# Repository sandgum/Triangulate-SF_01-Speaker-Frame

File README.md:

# Triangulate-SF_01-Speaker-Frame

*AI Use: No AI was used to generate any journal entries at all. AI was only used for electronics review and firmware help*

## Description
The SF_01 is a 24-inch digital picture frame running Android on a Raspberry Pi CM4. The Pi pushes an image to an off-the-shelf IPS monitor from LG through HDMI, and has wireless and USB peripheral support for touch displays, keyboards, and other HIDs.

The SF_01 also has a total 220W RMS speaker system on board, with 6 3.5-inch bass-mid woofers, and 4 0.75-inch tweeterspointing outwards from all four corners.

The frame itself is 3D-printed, with a large stand secured by VESA mount screws driven into the back of the monitor.

The frame has a separate circuit on board for audio playback, with an ESP32-S3 WROOM 2 module at its heart. It decodes a stereo Bluetooth A2DP stream, performs DSP calculations on board, and outputs two different I2S signals (one for the bass-mid woofers, the other for the tweeters).

After going through a DAC, the audio signals are routed through a custom analog multiplexer circuit to all 10 drivers, dynamically switching stereo output between drivers depending on the orientation of the frame.

The ESP32 appears in a device's Bluetooth list as a speaker, and it also runs a GATT server that is controlled by a Bluetooth LE connection via a custom iPhone app. Equalisers and crossovers can be set in the app.

### Woofer Layout

```
(1) ---------- (2)
(3)            (4)
(5) ---------- (6)
```

### Tweeter Layout

```
(1) ---------- (2)
 |              |
(3) ---------- (4)
```

**Landscape Orientation:**
* Left Channel:
* Woofers 1, 3, 5
* Tweeters 1, 3

* Right Channel:
* Woofers 2, 4, 6
* Tweeters 2, 4
  
**Portrait Orientation:**

* Left Channel:
* Woofers 5, 6
* Tweeters 3, 4

* Right Channel:
* Woofers 1, 2
* Tweeters 1, 2

* **Centre Channel: (Average of Right and Left):**
* Woofers 3, 4

## Built Prototype Images

## 3D Model Images

## PCB Schematics

**Raspberry Pi Circuit**

**DAC and Analog Multiplexer Circuit**

**ESP32 WROVER E Circuit**

**Subwoofer Amplifiers**

**Tweeter Amplifiers**

**Environmental and Orientation Sensors**

**Power Circuitry**

## PCB Layout

**Top Layer**

**Inner Layer 1 (GND Plane)**

**Inner Layer 2**

**Bottom Layer**

**3D Model**

## Bill Of Materials

Quantities are **per board**. Prices are LCSC unit pricing at low volume and drop at quantity. Everything except the Compute Module, drivers and panel is sourced from LCSC.

### Board Components

| Designators | Qty | Value | Part Number | Manufacturer | Package | Description | Unit (USD) | Ext. (USD) | LCSC |
|---|---|---|---|---|---|---|---|---|---|
| C1, C4, C5, C7, C9, C14, C17, C19, C23, C26, C28, C31, C34, C37, C38, C39, C42, C43, C45, C47, C50, C53, C72, C74, C80, C81, C106, C109, C135, C138, C163, C166, C185, C186, C189 | 35 | 100nF | CL10B104KB8NNNC | Samsung Electro-Mechanics | 0603 | 100nF ±10% 50V X7R 0603 | 0.0142 | 0.50 | [C1591](https://www.lcsc.com/product-detail/C1591.html) |
| C49, C52, C61, C62, C67, C68, C79, C82, C92, C93, C94, C95, C107, C108, C119, C120, C121, C122, C136, C137, C149, C150, C151, C152, C164, C165, C177, C178, C179, C180 | 30 | 1nF | CL10C102JB8NNNC | Samsung Electro-Mechanics | 0603 | 1nF ±5% 50V C0G 0603 | 0.0076 | 0.23 | [C163508](https://www.lcsc.com/product-detail/C163508.html) |
| C2, C8, C12, C13, C40, C41, C44, C46, C48, C75, C76, C77, C102, C103, C105, C131, C132, C134, C157, C158, C159, C160, C162, C188, C190 | 25 | 1uF | CL10B105KA8NNNC | Samsung Electro-Mechanics | 0603 | 1uF ±10% 25V X7R 0603 | 0.0218 | 0.55 | [C29936](https://www.lcsc.com/product-detail/C29936.html) |
| C24, C63, C64, C69, C70, C96, C97, C98, C99, C123, C124, C125, C126, C153, C154, C155, C156, C181, C182, C183, C184 | 21 | 10nF | GRM1885C1H103JA01D | muRata | 0603 | 10nF ±5% 50V C0G 0603 | 0.0547 | 1.15 | [C85973](https://www.lcsc.com/product-detail/C85973.html) |
| C55, C56, C57, C58, C84, C85, C86, C87, C111, C112, C113, C114, C141, C142, C143, C144, C169, C170, C171, C172 | 20 | 220nF | CL10B224KB8NNNC | Samsung Electro-Mechanics | 0603 | 220nF ±10% 50V X7R 0603 | 0.0121 | 0.24 | [C64705](https://www.lcsc.com/product-detail/C64705.html) |
| C59, C60, C65, C66, C88, C89, C90, C91, C115, C116, C117, C118, C145, C146, C147, C148, C173, C174, C175, C176 | 20 | 680nF | CGA3E3X5R1H684KT0Y0N | TDK | 0603 | 680nF ±10% 50V X5R 0603 | 0.1052 | 2.10 | [C694504](https://www.lcsc.com/product-detail/C694504.html) |
| C10, C11, C35, C36, C71 | 5 | 2.2nF | CL10B222KB8NNNC | Samsung Electro-Mechanics | 0603 | 2.2nF ±10% 50V X7R 0603 | 0.0061 | 0.03 | [C16033](https://www.lcsc.com/product-detail/C16033.html) |
| C20, C21, C29, C30 | 4 | 2.2uF | CL10A225KA8NNNC | Samsung Electro-Mechanics | 0603 | 2.2uF ±10% 25V X5R 0603 | 0.0231 | 0.09 | [C57895](https://www.lcsc.com/product-detail/C57895.html) |
| C6 | 1 | 22uF | CL10A226MP8NUNE | Samsung Electro-Mechanics | 0603 | 22uF ±20% 10V X5R 0603 | 0.0825 | 0.08 | [C86295](https://www.lcsc.com/product-detail/C86295.html) |
| C187 | 1 | 6.8pF | CC0603BRNPO9BN6R8 | YAGEO | 0603 | 6.8pF 50V NP0 0603 | 0.0038 | 0.00 | [C519114](https://www.lcsc.com/product-detail/C519114.html) |
| C130 | 1 | 7.5nF | GRM1885C1H752JA01D | muRata | 0603 | 7.5nF ±5% 50V C0G 0603 | 0.0156 | 0.02 | [C907758](https://www.lcsc.com/product-detail/C907758.html) |
| C100, C101, C129 | 3 | 10uF/50V | GRM32ER71H106KA12L | muRata | 1210 | 10uF ±10% 50V X7R 1210 | 0.3758 | 1.13 | [C77102](https://www.lcsc.com/product-detail/C77102.html) |
| C191, C192 | 2 | 47uF | GRM32ER61C476KE15L | muRata | 1210 | 47uF ±10% 16V X5R 1210 | 0.4273 | 0.85 | [C77101](https://www.lcsc.com/product-detail/C77101.html) |
| C51, C54, C78, C83, C104, C110, C133, C139, C161, C167 | 10 | 220uF | RVT35V220M6X8 | JIERR | SMD,D6.3xL7.7mm | 220uF ±20% 35V aluminium electrolytic 105C | 0.1003 | 1.00 | [C47023115](https://www.lcsc.com/product-detail/C47023115.html) |
| C3 | 1 | 10uF | EEEFTH100UAR | Panasonic | SMD,D4xL5.8mm | 10uF ±20% 50V aluminium electrolytic 105C | 0.1811 | 0.18 | [C242129](https://www.lcsc.com/product-detail/C242129.html) |
| C15, C16, C18, C22, C25, C27, C32, C33 | 8 | 10uF | EEEFTH100UAR | Panasonic | SMD,D4xL5.8mm | 10uF ±20% 50V aluminium electrolytic 105C | 0.1811 | 1.45 | [C242129](https://www.lcsc.com/product-detail/C242129.html) |
| C73 | 1 | 22uF | EEEFN1E220R | Panasonic | SMD,D4xL5.8mm | 22uF ±20% 25V aluminium electrolytic 105C | 0.1796 | 0.18 | [C494818](https://www.lcsc.com/product-detail/C494818.html) |
| R16, R18, R20, R26, R27, R30, R35, R36, R39, R45, R46, R50, R55, R56, R60, R76 | 16 | 100K | FRC0603J104TS | FOJAN | 0603 | 100kOhm ±5% 100mW 0603 | 0.0019 | 0.03 | [C2907088](https://www.lcsc.com/product-detail/C2907088.html) |
| R4, R12, R67, R68, R69, R70, R71, R77 | 8 | 10K | CRCW060310K0FKEA | VISHAY | 0603 | 10kOhm ±1% 100mW 0603 | 0.0057 | 0.05 | [C844918](https://www.lcsc.com/product-detail/C844918.html) |
| R21, R22, R23, R24, R31, R32, R33, R34, R40, R41, R42, R43, R51, R52, R53, R54, R61, R62, R63, R64 | 20 | 3.3R | FRC0805J3R3TS | FOJAN | 0805 | 3.3Ohm ±5% 125mW 0805 | 0.0037 | 0.07 | [C2907317](https://www.lcsc.com/product-detail/C2907317.html) |
| R15 | 1 | 3.3R | FRC0603F3R30TS | FOJAN | 0603 | 3.3Ohm ±1% 100mW 0603 | 0.0025 | 0.00 | [C2930016](https://www.lcsc.com/product-detail/C2930016.html) |
| R25, R44, R49, R59 | 4 | 100R | FRC0603F1000TS | FOJAN | 0603 | 100Ohm ±1% 100mW 0603 | 0.0021 | 0.01 | [C2906981](https://www.lcsc.com/product-detail/C2906981.html) |
| R28, R37, R47, R57 | 4 | 47K | FRC0603F4702TS | FOJAN | 0603 | 47kOhm ±1% 100mW 0603 | 0.0023 | 0.01 | [C2907042](https://www.lcsc.com/product-detail/C2907042.html) |
| R29, R38, R48, R58 | 4 | 75K | FRC0603F7502TS | FOJAN | 0603 | 75kOhm ±1% 100mW 0603 | 0.0025 | 0.01 | [C2907067](https://www.lcsc.com/product-detail/C2907067.html) |
| R5, R6, R72, R73 | 4 | 1K | FRC0603F1001TS | FOJAN | 0603 | 1kOhm ±1% 100mW 0603 | 0.0014 | 0.01 | [C2907002](https://www.lcsc.com/product-detail/C2907002.html) |
| R1, R2 | 2 | 2.2K | FRC0603F2201TS | FOJAN | 0603 | 2.2kOhm ±1% 100mW 0603 | 0.0023 | 0.00 | [C2907005](https://www.lcsc.com/product-detail/C2907005.html) |
| R3, R65 | 2 | 5.1K | FRC0603F5101TS | FOJAN | 0603 | 5.1kOhm ±1% 100mW 0603 | 0.0023 | 0.00 | [C2907044](https://www.lcsc.com/product-detail/C2907044.html) |
| R7, R17 | 2 | 56K | 0603WAF5602T5E | UNI-ROYAL | 0603 | 56kOhm ±1% 100mW 0603 | 0.0081 | 0.02 | [C23206](https://www.lcsc.com/product-detail/C23206.html) |
| Q1 | 1 | BSS138 | BSS138 | Shikues | SOT-23 | N-channel logic-level MOSFET 50V 0.2A | 0.0191 | 0.02 | [C112239](https://www.lcsc.com/product-detail/C112239.html) |
| R19 | 1 | 20K | FRC0603F2002TS | FOJAN | 0603 | 20kOhm ±1% 100mW 0603 | 0.0020 | 0.00 | [C2907011](https://www.lcsc.com/product-detail/C2907011.html) |
| R8, R9, R10, R11 | 4 | 470R | FRC0603F4700TS | FOJAN | 0603 | 470Ohm ±1% 100mW 0603 | 0.0027 | 0.01 | [C2907041](https://www.lcsc.com/product-detail/C2907041.html) |
| R14, R78 | 2 | 220R | 0603WAF2200T5E | UNI-ROYAL | 0603 | 220Ohm ±1% 100mW 0603 | 0.0010 | 0.00 | [C22962](https://www.lcsc.com/product-detail/C22962.html) |
| R66 | 1 | 205K | FRC0603F2053TS | FOJAN | 0603 | 205kOhm ±1% 100mW 0603 | 0.0008 | 0.00 | [C5126104](https://www.lcsc.com/product-detail/C5126104.html) |
| R75 | 1 | 60.4K | 0603WAF6042T5E | UNI-ROYAL | 0603 | 60.4kOhm ±1% 100mW 0603 | 0.0009 | 0.00 | [C23089](https://www.lcsc.com/product-detail/C23089.html) |
| R74 | 1 | 11.5K | FRC0603F1152TS | FOJAN | 0603 | 11.5kOhm ±1% 100mW 0603 | 0.0009 | 0.00 | [C2930057](https://www.lcsc.com/product-detail/C2930057.html) |
| R13 | 1 | 10.7K | FRC0603F1072TS | FOJAN | 0603 | 10.7kOhm ±1% 100mW 0603 | 0.0025 | 0.00 | [C5153968](https://www.lcsc.com/product-detail/C5153968.html) |
| L1, L2, L3, L4, L5, L6, L7, L8, L9, L10, L11, L12 | 12 | 10uH/10A | SMDRH104R-100MT | cjiang | SMD,10.4x10.3mm | 10uH ±20% 3.8A rated / 5.6A sat / 35mOhm | 0.1916 | 2.30 | [C9935](https://www.lcsc.com/product-detail/C9935.html) |
| L13, L14, L15, L16, L17, L18, L19, L20 | 8 | 10uH/3A | FHD4020S-100MT | cjiang | SMD,4x4mm | 10uH ±20% 2.35A rated / 3.5A sat / 190mOhm | 0.1102 | 0.88 | [C602032](https://www.lcsc.com/product-detail/C602032.html) |
| L21 | 1 | 6.8uH/6.6A | AAPS0650M6R8F | Coilank | SMD,6.6x6.4mm | 6.8uH ±20% 6.6A rated / 7A sat / 25.4mOhm molded | 0.9665 | 0.97 | [C49261484](https://www.lcsc.com/product-detail/C49261484.html) |
| U4 | 1 | TPS54540DDAR | TPS54540DDAR | Texas Instruments | SOIC-8-EP | 42V 5A step-down converter | 1.4638 | 1.46 | [C95286](https://www.lcsc.com/product-detail/C95286.html) |
| CR2 | 1 | STPS30H100DJF-TR | STPS30H100DJF-TR | ST | PowerFLAT5x6-8 | 100V 30A Schottky | 1.3985 | 1.40 | [C2969851](https://www.lcsc.com/product-detail/C2969851.html) |
| U10 | 1 | LP5907MFX-4.5 | LP5907MFX-4.5/NOPB | Texas Instruments | SOT-23-5 | 4.5V LDO | 0.5581 | 0.56 | [C529554](https://www.lcsc.com/product-detail/C529554.html) |
| U11 | 1 | LP5907MFX-3.3 | LP5907MFX-3.3 | Texas Instruments | SOT-23-5 | 3.3V LDO | 0.1343 | 0.13 | [C23380874](https://www.lcsc.com/product-detail/C23380874.html) |
| U17, U18, U19 | 3 | TPA3116D2DAD | TPA3116D2DADR | Texas Instruments | HTSSOP-32-6.1mm | 2x50W@4ohm Class D amplifier | 1.0619 | 3.19 | [C50144](https://www.lcsc.com/product-detail/C50144.html) |
| U20, U21 | 2 | TPA3130D2DAPR | TPA3130D2DAPR | Texas Instruments | HTSSOP-32-EP-6.1mm | 2x15W@8ohm Class D amplifier | 0.6314 | 1.26 | [C95206](https://www.lcsc.com/product-detail/C95206.html) |
| U12, U13, U15, U16, U24, U25, U26 | 7 | TS5A3159AYZPR | TS5A3159AYZPR | Texas Instruments | WCSP-6(1.4x0.9) | SPDT analog switch | 0.3971 | 2.78 | [C2651909](https://www.lcsc.com/product-detail/C2651909.html) |
| U5, U14 | 2 | PCM5102A | PCM5102APWR | Texas Instruments | TSSOP-20 | I2S stereo DAC | 1.3577 | 2.72 | [C107671](https://www.lcsc.com/product-detail/C107671.html) |
| U27 | 1 | TPS2041B | TPS2041BDBVR | Texas Instruments | SOT-23-5 | 500mA current-limited power switch | 0.3173 | 0.32 | [C51386](https://www.lcsc.com/product-detail/C51386.html) |
| U6 | 1 | RT9742SNGV | RT9742SNGV | RICHTEK | SOT-23-3 | 500mA high-side switch | 0.4386 | 0.44 | [C3235509](https://www.lcsc.com/product-detail/C3235509.html) |
| U9 | 1 | 74LVC1G07 | SN74LVC1G07DBVR | Texas Instruments | SOT-23-5 | Open-drain buffer 1.65-5.5V | 0.1109 | 0.11 | [C7829](https://www.lcsc.com/product-detail/C7829.html) |
| TP1–TP21, TP23–TP25 | 24 | TestPoint | — | — | 3.0x3.0mm pad / D2.5mm pad / D2.0mm plated hole | Bare copper - nothing to buy. 3 top, 4 plated through-hole, 17 on the bottom layer | 0.0000 | 0.00 | — |
| U28 | 1 | ESP32-WROVER-E-N16R8 | ESP32-WROVER-E-N16R8 | ESPRESSIF | SMD,31.4x18mm | WiFi/BT module 16MB flash 8MB PSRAM | 5.7127 | 5.71 | [C529589](https://www.lcsc.com/product-detail/C529589.html) |
| U22 | 1 | MPU-6050 | MPU-6050 | TDK InvenSense | QFN-24-EP(4x4) | 6-axis IMU | 6.3857 | 6.39 | [C24112](https://www.lcsc.com/product-detail/C24112.html) |
| U23 | 1 | BME680 | BME680 | Bosch | LGA-8 | Environmental sensor | 8.0629 | 8.06 | [C125972](https://www.lcsc.com/product-detail/C125972.html) |
| U2, U3, U7 | 3 | TPD4E02B04DQA | TPD4E02B04DQAR | Texas Instruments | USON-10(1x2.5) | 4-channel ESD array | 0.0996 | 0.30 | [C106794](https://www.lcsc.com/product-detail/C106794.html) |
| CR1 | 1 | SP3010-04UTG | SP3010-04UTG | Littelfuse | UFDFN-10(1x2.5) | 4-channel TVS array | 0.2544 | 0.25 | [C126837](https://www.lcsc.com/product-detail/C126837.html) |
| D1 | 1 | SMAJ26A | SMAJ26A | GOODWORK | DO-214AC(SMA) | 26V unidirectional TVS 400W Vbr 28.9V Vc 42.1V@9.5A | 0.0333 | 0.03 | [C2848697](https://www.lcsc.com/product-detail/C2848697.html) |
| D2, D5, D6, D7 | 4 | WS2812B | WS2812B-V6 | Worldsemi | SMD5050-4P | Addressable RGB LED | 0.1009 | 0.40 | [C52917433](https://www.lcsc.com/product-detail/C52917433.html) |
| D3, D4 | 2 | LED | YLED0603B | YONGYUTAI | 0603 | Blue LED 2.6-3.2V | 0.0058 | 0.01 | [C19171394](https://www.lcsc.com/product-detail/C19171394.html) |
| J1 | 1 | SS-53200-001 | HDMI 19PIN 043 | SHOU HAN | SMD | HDMI-A receptacle right angle | 0.1365 | 0.14 | [C2858275](https://www.lcsc.com/product-detail/C2858275.html) |
| J5, J6, J7, J8, J9, J10, J11, J12, J13, J14 | 10 | Speaker out | S2B-XH-A(LF)(SN) | JST | TH Right Angle P=2.5mm | 2-position 2.5mm header 3A | 0.0615 | 0.62 | [C157931](https://www.lcsc.com/product-detail/C157931.html) |
| J15 | 1 | USB_C_Receptacle_USB2.0_16P | TYPE-C 16PIN 2MD(073) | SHOU HAN | SMD | USB-C receptacle 16P | 0.0707 | 0.07 | [C2765186](https://www.lcsc.com/product-detail/C2765186.html) |
| J2 | 1 | Barrel_Jack | RAPC10U | Switchcraft | - | Power barrel jack 1.93/5.75mm | 17.0122 | 17.01 | [C3095802](https://www.lcsc.com/product-detail/C3095802.html) |
| J3 | 1 | UART | PZ254V-11-04P | XFCN | TH P=2.54mm | 4-position 2.54mm header | 0.0254 | 0.03 | [C2691448](https://www.lcsc.com/product-detail/C2691448.html) |
| SW1 | 1 | POWER | KSC931JLFS | C&K | SMD-4P,6.2x6.2mm | Tactile switch SPST IP67 J-lead | 2.0503 | 2.05 | [C221769](https://www.lcsc.com/product-detail/C221769.html) |
| SW2, SW3, SW4 | 3 | Tactile | KMR211GLFS | C&K | SMD | Tactile switch SPST-NO | 0.6377 | 1.91 | [C221675](https://www.lcsc.com/product-detail/C221675.html) |
| SW6 | 1 | SW_DPDT_x2 | JS202011JAQN | C&K | SMD | Slide switch DPDT 300mA@6V, right-angle | 1.2032 | 1.20 | [C221664](https://www.lcsc.com/product-detail/C221664.html) |
| U1 | 1 | CM4102008 | CM4102008 | Raspberry Pi | - | Compute Module 4 | 124.9100 | 124.91 | — |

**Board subtotal: $197.63 per board**

### Off-Board / Mechanical

| Qty | Item | Part Number | Manufacturer | Description | Unit (USD) | Ext. (USD) |
|---|---|---|---|---|---|---|
| 6 | Woofer | PLS-P830985 | Peerless by Tymphany | 3.95ohm full-range 30W driver | 18.74 | 112.45 |
| 4 | Tweeter | ND16FA-6 | Dayton Audio | Neodymium dome tweeter | 12.47 | 49.88 |
| 1 | Display | 24U411A-B | LG | 23.8in IPS FHD 120Hz panel | 74.53 | 74.53 |

**Off-board subtotal: $236.86**

### Items Needing Attention

| Designators | Status | Note |
|---|---|---|
| C100, C101, C129 | CHANGED + FOOTPRINT | Was 10uF/25V 0603 on the 24V rail. 10uF/50V does not exist in 0603 - the footprint has to go to 1210 |
| C191, C192 | CHANGED + FOOTPRINT | TPS54540 output bulk. 47uF does not exist in 0603 or 0805 at >=16V - footprint has to go to 1210 |
| L21 | CHANGED - NO PCB CHANGE | Now AAPS0650M6R8F (Coilank), 6.6A rated / 7A sat / 25.4mOhm. Replaced VLS6045EX-6R8M which saturated at full load (4.7A sat vs a 4.72A peak). 48% saturation margin now, and half the DCR. Body 6.6x6.4mm fits the existing 7.50x6.80mm courtyard so the land pattern is unchanged |
| CR2, R8-R11, R13, SW1, SW6 | CHANGED - RESTOCK | All five originals hit 0 stock on LCSC. CR2 -> STPS30H100DJF-TR (C2969851, same PowerFLAT 5x6 family, 100V, lowest Vf of the in-stock options). R8-R11 -> FRC0603F4700TS (C2907041). R13 -> FRC0603F1072TS (C5153968, only 1k in stock; plain 10K works as a fallback). SW1 -> KSC931JLFS (C221769, only 18 in stock). SW6 -> JS202011JAQN (C221664) which is RIGHT-ANGLE where the original was VERTICAL, so verify the land pattern |
| U8 | DELETED | U8 buffered CM4 RUN_PG into the GLOBAL_EN button, forming a feedback loop that repeatedly power-cycled the module. Removed. SW1 now goes straight to GPIO3/GND as a soft power button (`dtoverlay=gpio-shutdown`), with R77 as pull-up and C74 as debounce |
| U9 | CHANGED - FOOTPRINT | Footprint is SOT-23-5, same as U10/U11/U27; symbol pin numbering unchanged (1=NC 2=A 3=GND 4=Y 5=VCC). MUST stay LVC. Budget alt C7394020 (UMW) |
| R77, R78, C74, TP1, TP2 | NEW | Power-button circuit. R77 10K pulls GPIO3 to 3V3, C74 100nF debounces it, R78 220R feeds TP1 for CM4 reset (220R is the value the CM4 datasheet specifies), TP2 exposes GLOBAL_EN for a hard force-off |
| D2, D5, D6, D7 | KEEP - RAIL ISSUE | Datasheet minimum VDD is 3.5V and these sit on the 3.3V rail. See review B5 |
| J1 | VERIFY | Footprint is drawn for the Stewart SS-53200-001 but the sourced part is SHOU HAN - confirm the land patterns match before ordering |
| J5, J6, J7, J8, J9, J10, J11, J12, J13, J14 | KEEP - MARGINAL | Rated 3A but a 50W/4ohm woofer channel draws 3.5A RMS. See review H9 |
| J2 | KEEP - VERIFY RATING | Confirm its current rating against the ~8A this board can draw at full output |
| U1 | NOT ON LCSC | Source from an approved Raspberry Pi reseller. Schematic says CM4102008 but the old BOM said CM4102016 - pick one |

## Total: $434.49 USD per complete unit

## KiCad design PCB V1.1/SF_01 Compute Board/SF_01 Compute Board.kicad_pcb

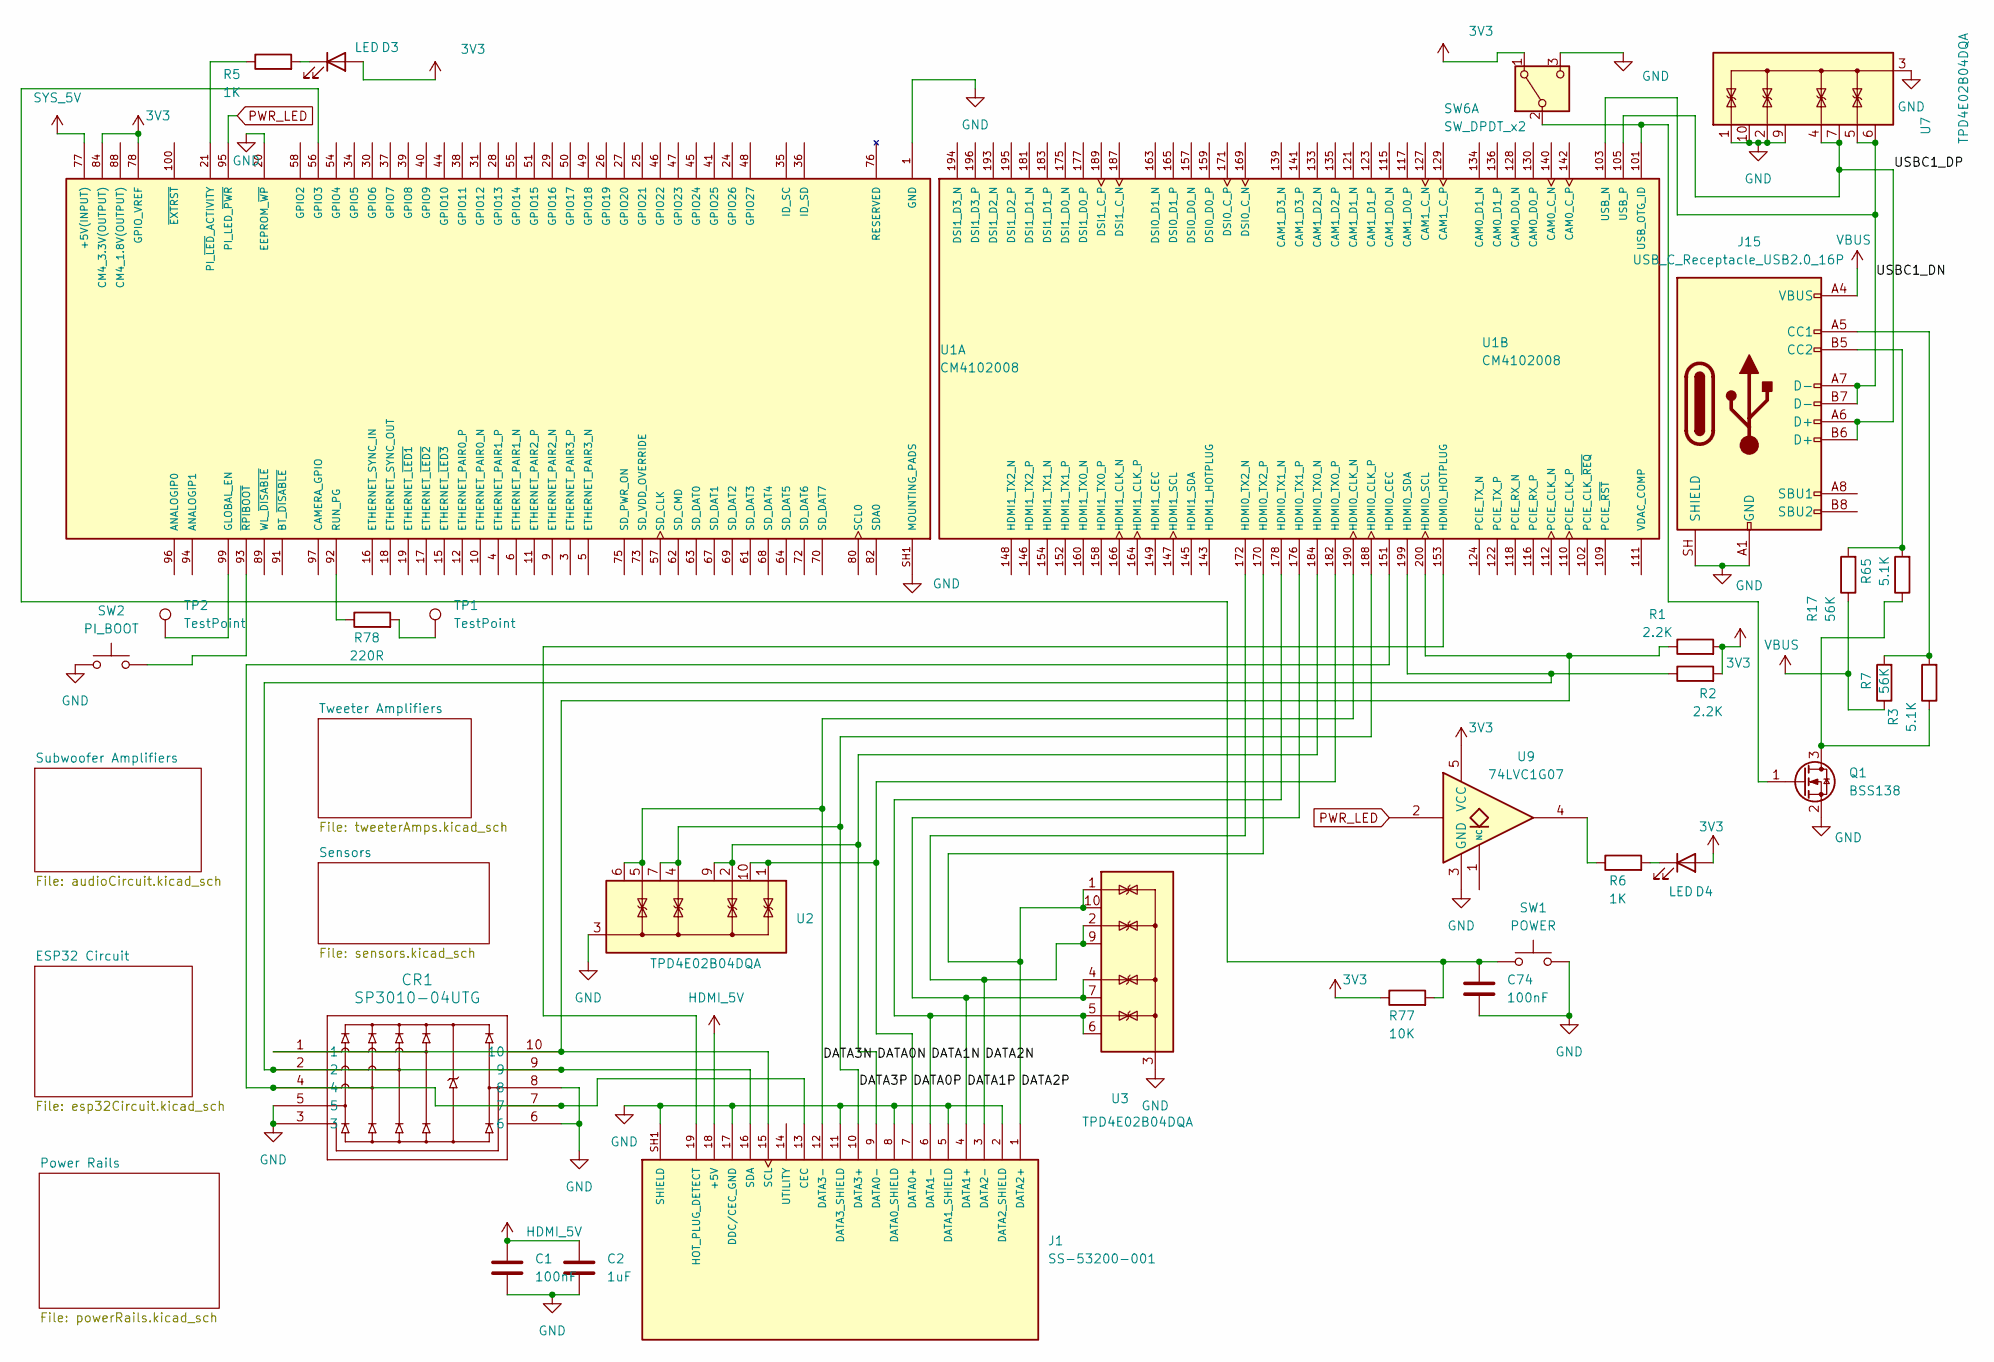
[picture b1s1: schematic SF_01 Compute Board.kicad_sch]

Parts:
C1, C74: 100nF; C_0603_1608Metric
C2: 1uF; C_0603_1608Metric
CR1: SP3010-04UTG; UDFEN-10_MO229_LTF
D3, D4: LED; LED_0603_1608Metric
J1: SS-53200-001; STEWART_SS-53200-001; PARTREV A0
J15: USB_C_Receptacle_USB2.0_16P; USB_C_Receptacle_HCTL_HC-TYPE-C-16P-01A
Q1: BSS138; SOT-23
R1, R2: 2.2K; R_0603_1608Metric
R3, R65: 5.1K; R_0603_1608Metric
R5, R6: 1K; R_0603_1608Metric
R7, R17: 56K; R_0603_1608Metric
R77: 10K; R_0603_1608Metric
R78: 220R; R_0603_1608Metric
SW1: POWER; SW_Push_1P1T_NO_CK_KSC9xxJ
SW2: PI_BOOT; SW_Push_1P1T-SH_NO_CK_KMR2xxG
SW6: SW_DPDT_x2; SW_DPDT_CK_JS202011JCQN
TP1, TP2: TestPoint; TestPoint_Pad_3.0x3.0mm
U1: CM4102008; MODULE_CM4102008; PARTREV 2021-10-12
U2, U3, U7: TPD4E02B04DQA; USON-10_2.5x1.0mm_P0.5mm
U9: 74LVC1G07; SOT-23-5

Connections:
3V3: D3.2 (A), D4.2 (A), R1.2, R2.2, R77.1, SW6.1 (A), U1.78 (GPIO_VREF), U1.84 (CM4_3.3V(OUTPUT)), U1.86 (CM4_3.3V(OUTPUT)), U9.5 (VCC); also elsewhere on the board
/DATA0N: J1.9 (DATA0-), U1.184 (HDMI0_TX0_N), U2.2 (IO2), U2.9 (NC)
/DATA0P: J1.7 (DATA0+), U1.182 (HDMI0_TX0_P), U2.1 (IO1), U2.10 (NC)
/DATA1N: J1.6 (DATA1-), U1.178 (HDMI0_TX1_N), U3.5 (IO4), U3.6 (NC)
/DATA1P: J1.4 (DATA1+), U1.176 (HDMI0_TX1_P), U3.4 (IO3), U3.7 (NC)
/DATA2N: J1.3 (DATA2-), U1.172 (HDMI0_TX2_N), U3.2 (IO2), U3.9 (NC)
/DATA2P: J1.1 (DATA2+), U1.170 (HDMI0_TX2_P), U3.1 (IO1), U3.10 (NC)
/DATA3N: J1.12 (DATA3-), U1.190 (HDMI0_CLK_N), U2.5 (IO4), U2.6 (NC)
/DATA3P: J1.10 (DATA3+), U1.188 (HDMI0_CLK_P), U2.4 (IO3), U2.7 (NC)
/USBC1_DN: J15.A7 (D-), J15.B7 (D-), U1.103 (USB_N), U7.5 (IO4), U7.6 (NC)
/USBC1_DP: J15.A6 (D+), J15.B6 (D+), U1.105 (USB_P), U7.4 (IO3), U7.7 (NC)
CM4_1.8V(OUTPUT): U1.88 (CM4_1.8V(OUTPUT)), U1.90 (CM4_1.8V(OUTPUT))
HDMI_5V: C1.1, C2.1, J1.18 (+5V); also elsewhere on the board
unnamed: D3.1 (K), R5.2
unnamed: D4.1 (K), R6.2
unnamed: CR1.4, CR1.7, J1.13 (CEC), U1.151 (HDMI0_CEC)
unnamed: J1.19 (HOT_PLUG_DETECT), U1.153 (HDMI0_HOTPLUG)
unnamed: CR1.1, CR1.10, J1.15 (SCL), R1.1, U1.200 (HDMI0_SCL)
unnamed: CR1.2, CR1.9, J1.16 (SDA), R2.1, U1.199 (HDMI0_SDA)
unnamed: J15.A5 (CC1), R3.2, R7.2
unnamed: J15.B5 (CC2), R17.2, R65.2
unnamed: Q1.3 (D), R3.1, R65.1
unnamed: Q1.1 (G), SW6.2 (B), U1.101 (USB_OTG_ID)
unnamed: R6.1, U9.4
unnamed: R78.2, TP1.1 (1_1)
unnamed: TP2.1 (1_1), U1.99 (GLOBAL_EN)
unnamed: C74.1, R77.2, SW1.1, U1.56 (GPIO3)
unnamed: R5.1, U1.21 (PI_~LED_ACTIVITY)
unnamed: R78.1, U1.92 (RUN_PG)
unnamed: SW2.2, U1.93 (~RPIBOOT)
PWR_LED: U1.95 (PI_LED_~PWR), U9.2
VBUS: J15.A4 (VBUS), J15.A9 (VBUS), J15.B4 (VBUS), J15.B9 (VBUS), R7.1, R17.1; also elsewhere on the board

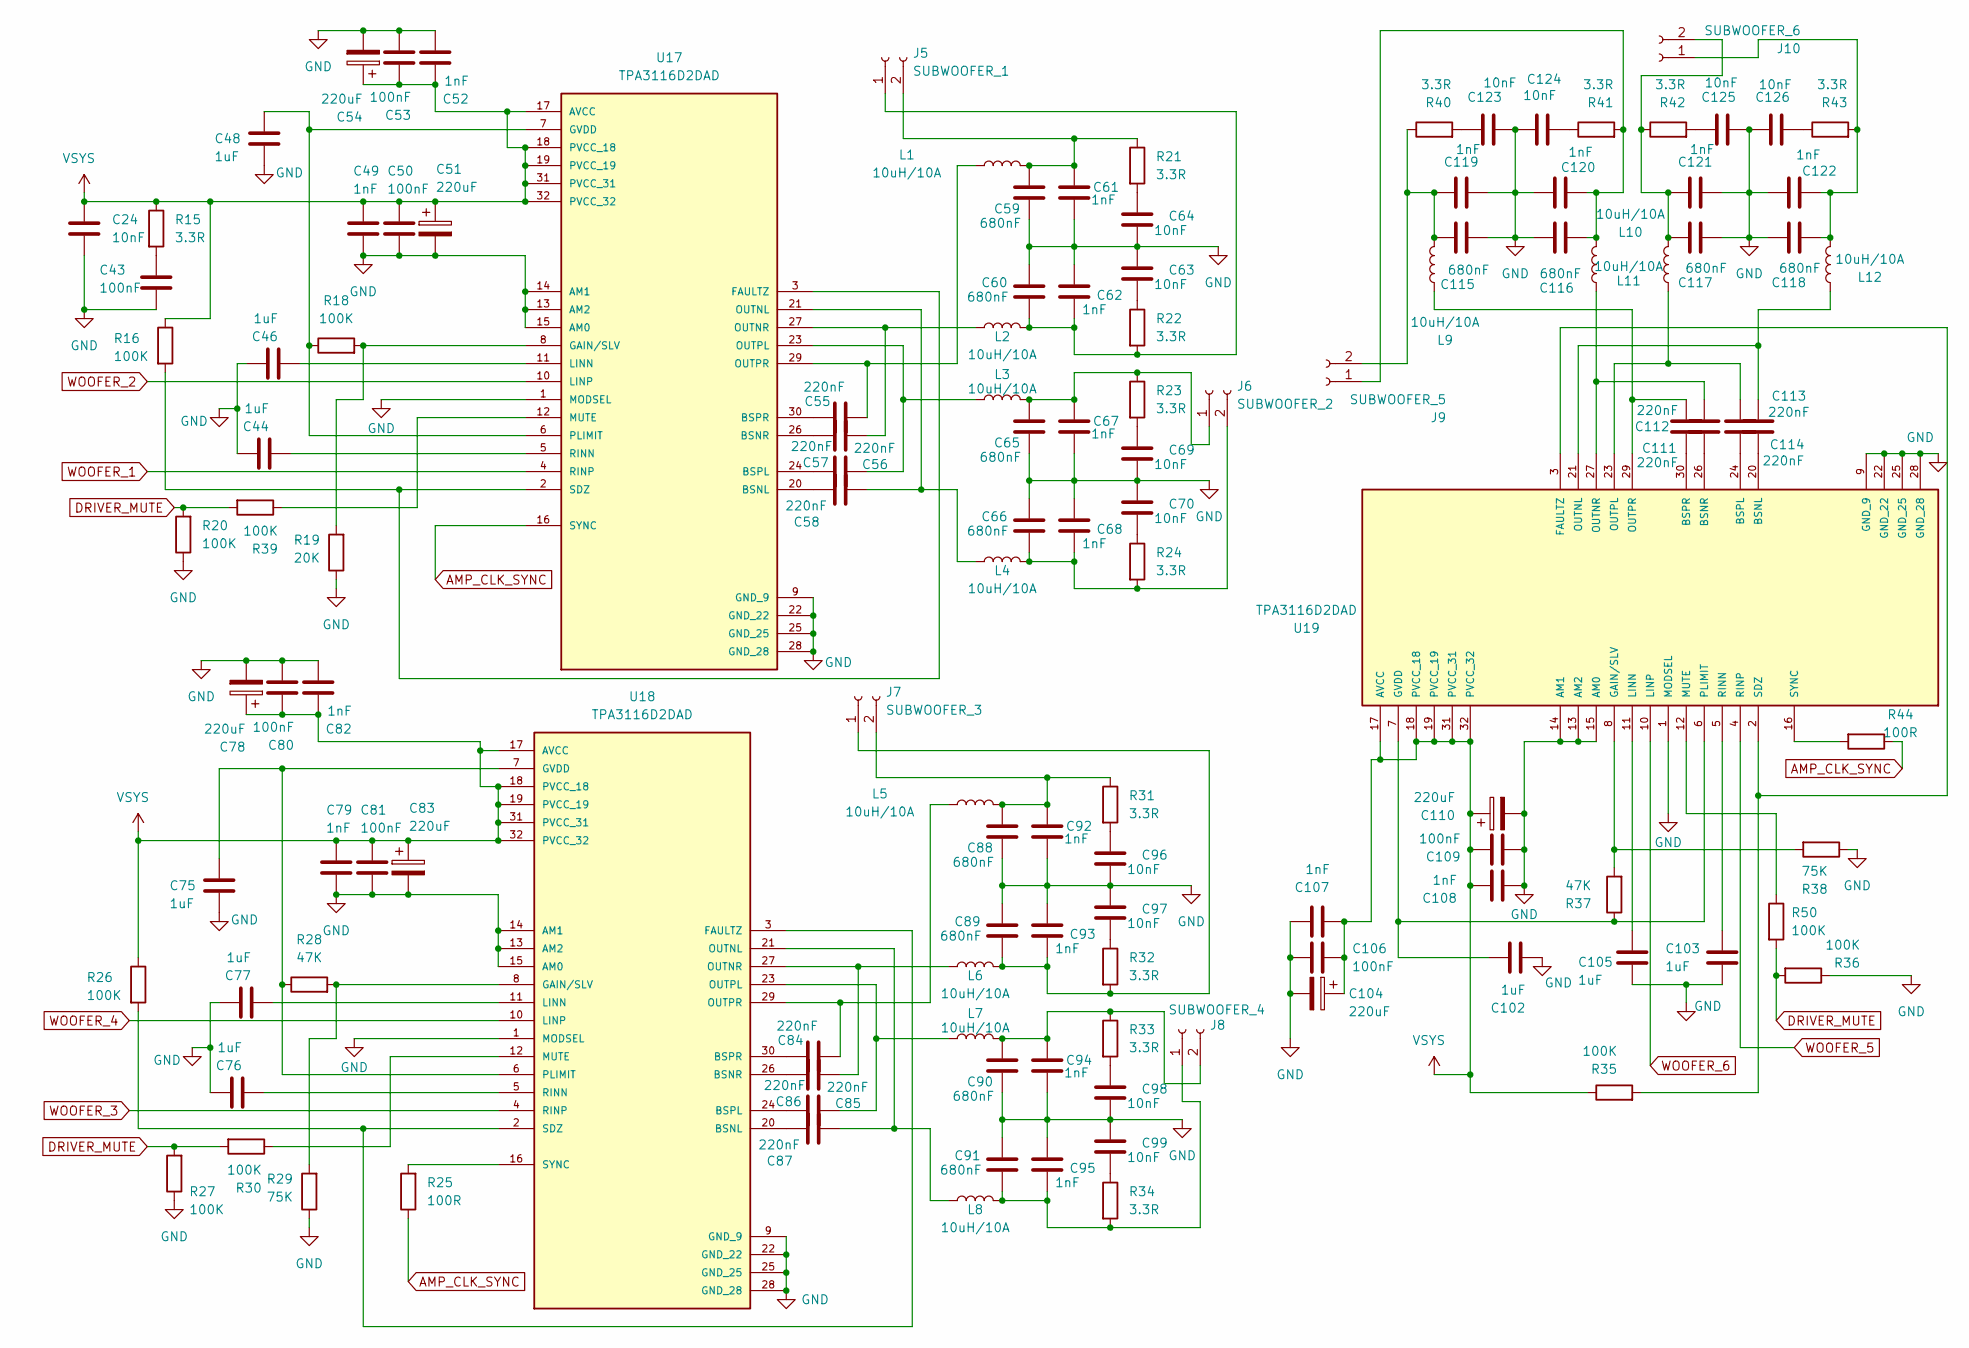
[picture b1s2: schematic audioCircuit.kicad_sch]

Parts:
C24, C63, C64, C69, C70, C96, C97, C98, C99, C123, C124, C125, C126: 10nF; C_0603_1608Metric
C43, C50, C53, C80, C81, C106, C109: 100nF; C_0603_1608Metric
C44, C46, C48, C75, C76, C77, C102, C103, C105: 1uF; C_0603_1608Metric
C49, C52, C61, C62, C67, C68, C79, C82, C92, C93, C94, C95, C107, C108, C119, C120, C121, C122: 1nF; C_0603_1608Metric
C51, C54, C78, C83, C104, C110: 220uF; CP_Elec_6.3x9.9
C55, C56, C57, C58, C84, C85, C86, C87, C111, C112, C113, C114: 220nF; C_0603_1608Metric
C59, C60, C65, C66, C88, C89, C90, C91, C115, C116, C117, C118: 680nF; C_0603_1608Metric
J5: SUBWOOFER_1; JST_XH_S2B-XH-A-1_1x02_P2.50mm_Horizontal
J6: SUBWOOFER_2; JST_XH_S2B-XH-A-1_1x02_P2.50mm_Horizontal
J7: SUBWOOFER_3; JST_XH_S2B-XH-A-1_1x02_P2.50mm_Horizontal
J8: SUBWOOFER_4; JST_XH_S2B-XH-A-1_1x02_P2.50mm_Horizontal
J9: SUBWOOFER_5; JST_XH_S2B-XH-A-1_1x02_P2.50mm_Horizontal
J10: SUBWOOFER_6; JST_XH_S2B-XH-A-1_1x02_P2.50mm_Horizontal
L1, L2, L3, L4, L5, L6, L7, L8, L9, L10, L11, L12: 10uH/10A; L_10.4x10.4_H4.8
R15: 3.3R; R_0603_1608Metric
R16, R18, R20, R26, R27, R30, R35, R36, R39, R50: 100K; R_0603_1608Metric
R19: 20K; R_0603_1608Metric
R21, R22, R23, R24, R31, R32, R33, R34, R40, R41, R42, R43: 3.3R; R_0805_2012Metric
R25, R44: 100R; R_0603_1608Metric
R28, R37: 47K; R_0603_1608Metric
R29, R38: 75K; R_0603_1608Metric
U17, U18, U19: TPA3116D2DAD; SOP65P810X115-32N; PARTREV G

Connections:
AMP_CLK_SYNC: R25.1, R44.1, U17.16 (SYNC); also elsewhere on the board
DRIVER_MUTE: R20.2, R27.2, R30.2, R36.2, R39.2, R50.2; also elsewhere on the board
unnamed: C43.1, R15.2
unnamed: C63.1, R22.1
unnamed: C64.2, R21.2
unnamed: C69.2, R23.2
unnamed: C70.1, R24.1
unnamed: C96.2, R31.2
unnamed: C97.1, R32.1
unnamed: C98.2, R33.2
unnamed: C99.1, R34.1
unnamed: C123.2, R40.2
unnamed: C124.1, R41.1
unnamed: C125.2, R42.2
unnamed: C126.1, R43.1
unnamed: C60.1, C62.1, J5.1, L2.2, R22.2
unnamed: C59.2, C61.2, J5.2, L1.2, R21.1
unnamed: C65.2, C67.2, J6.1, L3.2, R23.1
unnamed: C66.1, C68.1, J6.2, L4.2, R24.2
unnamed: C89.1, C93.1, J7.1, L6.2, R32.2
unnamed: C88.2, C92.2, J7.2, L5.2, R31.1
unnamed: C91.1, C95.1, J8.1, L8.2, R34.2
unnamed: C90.2, C94.2, J8.2, L7.2, R33.1
unnamed: C116.1, C120.1, J9.1, L10.2, R41.2
unnamed: C115.2, C119.2, J9.2, L9.2, R40.1
unnamed: C118.1, C122.1, J10.1, L12.2, R43.2
unnamed: C117.2, C121.2, J10.2, L11.2, R42.1
unnamed: C58.1, U17.20 (BSNL)
unnamed: C56.1, U17.26 (BSNR)
unnamed: C57.1, U17.24 (BSPL)
unnamed: C55.1, U17.30 (BSPR)
unnamed: R16.2, U17.2 (SDZ), U17.3 (FAULTZ)
unnamed: R18.2, R19.2, U17.8 (GAIN/SLV)
unnamed: C48.2, R18.1, U17.6 (PLIMIT), U17.7 (GVDD)
unnamed: C46.2, U17.11 (LINN)
unnamed: R39.1, U17.12 (MUTE)
unnamed: C58.2, L4.1, U17.21 (OUTNL)
unnamed: C56.2, L2.1, U17.27 (OUTNR)
unnamed: C57.2, L3.1, U17.23 (OUTPL)
unnamed: C55.2, L1.1, U17.29 (OUTPR)
unnamed: C44.2, U17.5 (RINN)
unnamed: C87.1, U18.20 (BSNL)
unnamed: C85.1, U18.26 (BSNR)
unnamed: C86.1, U18.24 (BSPL)
unnamed: C84.1, U18.30 (BSPR)
unnamed: R26.2, U18.2 (SDZ), U18.3 (FAULTZ)
unnamed: R28.2, R29.2, U18.8 (GAIN/SLV)
unnamed: C75.2, R28.1, U18.6 (PLIMIT), U18.7 (GVDD)
unnamed: C77.2, U18.11 (LINN)
unnamed: R30.1, U18.12 (MUTE)
unnamed: C87.2, L8.1, U18.21 (OUTNL)
unnamed: C85.2, L6.1, U18.27 (OUTNR)
unnamed: C86.2, L7.1, U18.23 (OUTPL)
unnamed: C84.2, L5.1, U18.29 (OUTPR)
unnamed: C76.2, U18.5 (RINN)
unnamed: R25.2, U18.16 (SYNC)
unnamed: C114.1, U19.20 (BSNL)
unnamed: C112.1, U19.26 (BSNR)
unnamed: C113.1, U19.24 (BSPL)
unnamed: C111.1, U19.30 (BSPR)
unnamed: R35.2, U19.2 (SDZ), U19.3 (FAULTZ)
unnamed: R37.2, R38.2, U19.8 (GAIN/SLV)
unnamed: C102.2, R37.1, U19.6 (PLIMIT), U19.7 (GVDD)
unnamed: C105.2, U19.11 (LINN)
unnamed: R50.1, U19.12 (MUTE)
unnamed: C114.2, L12.1, U19.21 (OUTNL)
unnamed: C112.2, L10.1, U19.27 (OUTNR)
unnamed: C113.2, L11.1, U19.23 (OUTPL)
unnamed: C111.2, L9.1, U19.29 (OUTPR)
unnamed: C103.2, U19.5 (RINN)
unnamed: R44.2, U19.16 (SYNC)
VSYS: C24.1, C49.1, C50.1, C51.1, C52.1, C53.1, C54.1, C78.1, C79.1, C80.1, C81.1, C82.1, C83.1, C104.1, C106.1, C107.1, C108.1, C109.1, C110.1, R15.1, R16.1, R26.1, R35.1, U17.17 (AVCC), U17.18 (PVCC_18), U17.19 (PVCC_19), U17.31 (PVCC_31), U17.32 (PVCC_32), U18.17 (AVCC), U18.18 (PVCC_18), U18.19 (PVCC_19), U18.31 (PVCC_31), U18.32 (PVCC_32), U19.17 (AVCC), U19.18 (PVCC_18), U19.19 (PVCC_19), U19.31 (PVCC_31), U19.32 (PVCC_32); also elsewhere on the board
WOOFER_1: U17.4 (RINP); also elsewhere on the board
WOOFER_2: U17.10 (LINP); also elsewhere on the board
WOOFER_3: U18.4 (RINP); also elsewhere on the board
WOOFER_4: U18.10 (LINP); also elsewhere on the board
WOOFER_5: U19.4 (RINP); also elsewhere on the board
WOOFER_6: U19.10 (LINP); also elsewhere on the board

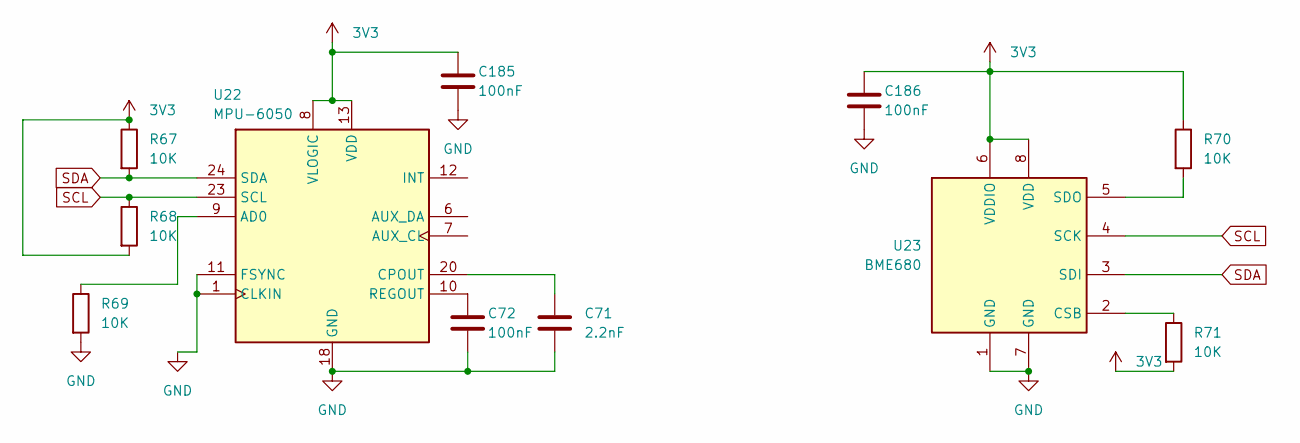
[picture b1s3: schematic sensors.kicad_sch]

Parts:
C71: 2.2nF; C_0603_1608Metric
C72, C185, C186: 100nF; C_0603_1608Metric
R67, R68, R69, R70, R71: 10K; R_0603_1608Metric
U22: MPU-6050; InvenSense_QFN-24_4x4mm_P0.5mm
U23: BME680; Bosch_LGA-8_3x3mm_P0.8mm_ClockwisePinNumbering

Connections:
3V3: C185.1, C186.1, R67.1, R68.2, R70.1, R71.2, U22.8 (VLOGIC), U22.13 (VDD), U23.6 (VDDIO), U23.8 (VDD); also elsewhere on the board
unnamed: R69.1, U22.9 (AD0)
unnamed: C71.1, U22.20 (CPOUT)
unnamed: C72.1, U22.10 (REGOUT)
unnamed: R71.1, U23.2 (CSB)
unnamed: R70.2, U23.5 (SDO)
SCL: R68.1, U22.23 (SCL), U23.4 (SCK); also elsewhere on the board
SDA: R67.2, U22.24 (SDA), U23.3 (SDI); also elsewhere on the board

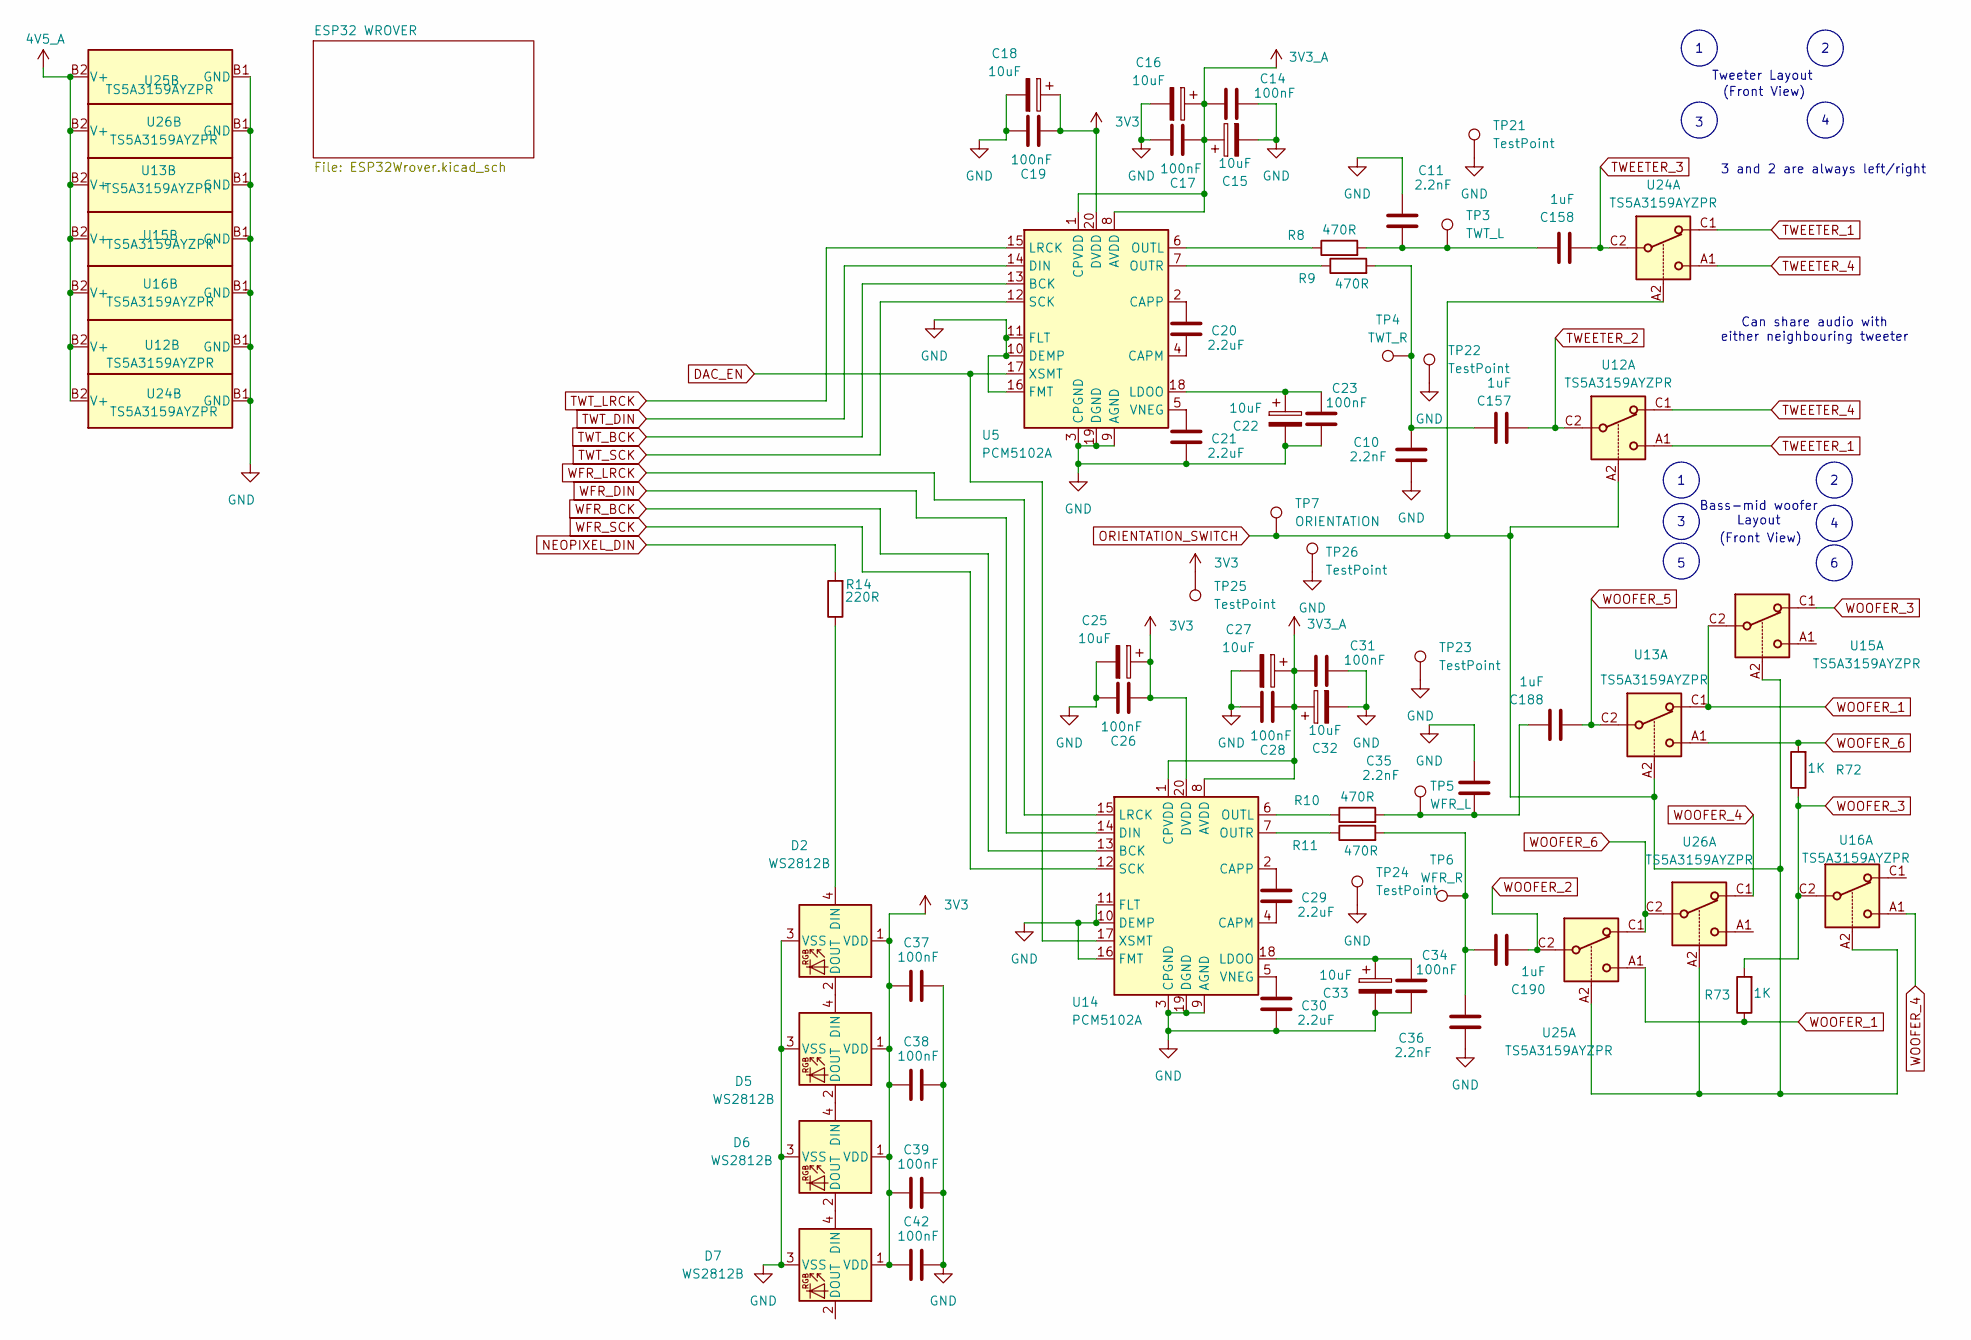
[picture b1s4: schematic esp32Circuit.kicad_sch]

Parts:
C10, C11, C35, C36: 2.2nF; C_0603_1608Metric
C14, C17, C19, C23, C26, C28, C31, C34, C37, C38, C39, C42: 100nF; C_0603_1608Metric
C15, C16, C18, C22, C25, C27, C32, C33: 10uF; CP_Elec_4x3
C20, C21, C29, C30: 2.2uF; C_0603_1608Metric
C157, C158, C188, C190: 1uF; C_0603_1608Metric
D2, D5, D6, D7: WS2812B; LED_WS2812B_PLCC4_5.0x5.0mm_P3.2mm
R8, R9, R10, R11: 470R; R_0603_1608Metric
R14: 220R; R_0603_1608Metric
R72, R73: 1K; R_0603_1608Metric
TP3: TWT_L; TestPoint_Plated_Hole_D2.0mm
TP4: TWT_R; TestPoint_Plated_Hole_D2.0mm
TP5: WFR_L; TestPoint_Plated_Hole_D2.0mm
TP6: WFR_R; TestPoint_Plated_Hole_D2.0mm
TP7: ORIENTATION; TestPoint_Pad_D2.5mm
TP21, TP22, TP23, TP24, TP25, TP26: TestPoint; TestPoint_Pad_D2.5mm
U5, U14: PCM5102A; TSSOP-20_4.4x6.5mm_P0.65mm
U12, U13, U15, U16, U24, U25, U26: TS5A3159AYZPR; Texas_DSBGA-6_0.9x1.4mm_Layout2x3_P0.5mm

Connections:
3V3: C18.1, C19.2, C25.1, C26.2, C37.2, C38.2, C39.2, C42.2, D2.1 (VDD), D5.1 (VDD), D6.1 (VDD), D7.1 (VDD), TP25.1 (1_1), U5.20 (DVDD), U14.20 (DVDD); also elsewhere on the board
3V3_A: C14.2, C15.1, C16.1, C17.2, C27.1, C28.2, C31.2, C32.1, U5.1 (CPVDD), U5.8 (AVDD), U14.1 (CPVDD), U14.8 (AVDD); also elsewhere on the board
DAC_EN: U5.17 (XSMT), U14.17 (XSMT); also elsewhere on the board
NEOPIXEL_DIN: R14.2; also elsewhere on the board
unnamed: C10.1, C157.1, R9.2, TP4.1 (1_1)
unnamed: C11.2, C158.1, R8.2, TP3.1 (1_1)
unnamed: C35.2, C188.1, R10.2, TP5.1 (1_1)
unnamed: C36.1, C190.1, R11.2, TP6.1 (1_1)
unnamed: D2.4 (DIN), R14.1
unnamed: D2.2 (DOUT), D5.4 (DIN)
unnamed: D5.2 (DOUT), D6.4 (DIN)
unnamed: D6.2 (DOUT), D7.4 (DIN)
unnamed: C20.2, U5.4 (CAPM)
unnamed: C20.1, U5.2 (CAPP)
unnamed: C22.1, C23.2, U5.18 (LDOO)
unnamed: R8.1, U5.6 (OUTL)
unnamed: R9.1, U5.7 (OUTR)
unnamed: C21.1, U5.5 (VNEG)
unnamed: C29.2, U14.4 (CAPM)
unnamed: C29.1, U14.2 (CAPP)
unnamed: C33.1, C34.2, U14.18 (LDOO)
unnamed: R10.1, U14.6 (OUTL)
unnamed: R11.1, U14.7 (OUTR)
unnamed: C30.1, U14.5 (VNEG)
ORIENTATION_SWITCH: TP7.1 (1_1), U12.A2, U13.A2, U15.A2, U16.A2, U24.A2, U25.A2, U26.A2; also elsewhere on the board
TWEETER_1: U12.A1, U24.C1; also elsewhere on the board
TWEETER_2: C157.2, U12.C2; also elsewhere on the board
TWEETER_3: C158.2, U24.C2; also elsewhere on the board
TWEETER_4: U12.C1, U24.A1; also elsewhere on the board
TWT_BCK: U5.13 (BCK); also elsewhere on the board
TWT_DIN: U5.14 (DIN); also elsewhere on the board
TWT_LRCK: U5.15 (LRCK); also elsewhere on the board
TWT_SCK: U5.12 (SCK); also elsewhere on the board
WFR_BCK: U14.13 (BCK); also elsewhere on the board
WFR_DIN: U14.14 (DIN); also elsewhere on the board
WFR_LRCK: U14.15 (LRCK); also elsewhere on the board
WFR_SCK: U14.12 (SCK); also elsewhere on the board
WOOFER_1: R73.1, U13.C1, U15.C2, U25.A1; also elsewhere on the board
WOOFER_2: C190.2, U25.C2; also elsewhere on the board
WOOFER_3: R72.1, R73.2, U15.C1, U16.C2; also elsewhere on the board
WOOFER_4: U16.A1, U26.C1; also elsewhere on the board
WOOFER_5: C188.2, U13.C2; also elsewhere on the board
WOOFER_6: R72.2, U13.A1, U25.C1, U26.C2; also elsewhere on the board

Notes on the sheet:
(Front View)
3 and 2 are always left/right
Can share audio with either neighbouring tweeter
Tweeter Layout
Bass-mid woofer Layout

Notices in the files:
parts and their libraries:
COPYRIGHT: Copyright (C) 2025 Ultra Librarian. All rights reserved.
